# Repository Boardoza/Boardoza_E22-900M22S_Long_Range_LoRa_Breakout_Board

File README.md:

# Boardoza E22-900M22S LoRa® Breakout Board

The **Boardoza E22-900M22S Breakout Board** is a compact long-range wireless communication board based on the **Ebyte E22-900M22S** LoRa® module. Powered by the **Semtech SX1262** RF transceiver, it supports both **LoRa®** and **FSK(Frequency Shift Keying)** modulation, enabling reliable low-power wireless communication over the **850–930 MHz ISM frequency range**, including the widely used **868 MHz** and **915 MHz** bands. The onboard **32 MHz TCXO (Temperature Compensated Crystal Oscillator)** provides excellent frequency stability, making it suitable for narrowband communication and outdoor deployments.

The breakout board exposes the module's **SPI interface**, RF control signals, and status pins through standard headers, allowing easy integration with development platforms such as **STM32**, **ESP32**, **Arduino, and other 3.3V-compatible microcontrollers**. With its SMA antenna connector, industrial operating temperature range, and long communication distance, this board is ideal for **IoT gateways, smart agriculture, telemetry, environmental monitoring, industrial automation, and wireless sensor networks**.

---

## Key Features

- **Long-Range LoRa® Communication:** Based on the Semtech SX1262 transceiver for reliable long-distance wireless links.
- **868 / 915 MHz ISM Band Support:** Compatible with license-free ISM bands used worldwide.
- **High RF Output Power:** Up to **22 dBm (160 mW)** transmit power with software-adjustable output levels.
- **LoRa® and FSK Modulation Support:** Provides air data rates from 0.018 to 62.5 kbps in LoRa® mode and up to 300 kbps in FSK mode.
- **Stable RF Performance:** Integrated **32 MHz TCXO** improves frequency stability over temperature.
- **Easy MCU Integration:** Standard **4-wire SPI interface** with dedicated control and status signals.
- **SMA Antenna Connector:** Ready for external antennas with improved RF performance.
- **Ideal for IoT Applications:** Suitable for wireless sensor networks, smart agriculture, telemetry, industrial monitoring, and remote data acquisition.

---

## Technical Specifications

**Model:** E22-900M22S   
**Manufacturer:** Boardoza    
**Manufacturer IC:** Chengdu Ebyte Electronic Technology Co., Ltd.   
**RF Transceiver:** Semtech SX1262  
**Input Voltage:** 3.3V – 5.5V     
**Interface:** SPI  
**Frequency Range:** 850 – 930 MHz     
**Maximum RF Output Power:** 22 dBm (160 mW)  
**Maximum Air Data Rate (LoRa®):** 0.018 to 62.5 kbps  
**Maximum Air Data Rate (FSK):** 300 kbps  
**FIFO Buffer:** 256 Bytes  
**Oscillator:** High-Precision 32 MHz TCXO  
**Antenna Connector:** SMA Female  
**Operating Temperature:** -40°C to +85°C  
**Board Dimensions:** 40 mm × 20 mm

---

## Board Pinout

### ( J1 ) SPI Interface

| Pin Number | Pin Name | Description |
|:---:|:---:|---|
| 1 | VCC | Power Input |
| 2 | MISO | SPI Data Output |
| 3 | MOSI | SPI Data Input |
| 4 | SCK | SPI Clock |
| 5 | nCS | SPI Chip Select (Active Low) |
| 6 | GND | Ground |

### ( J2 ) Control Signals

| Pin Number | Pin Name | Description |
|:---:|:---:|---|
| 1 | NRST | Reset Input (Active Low) |
| 2 | BUSY | Module Busy Status Output |
| 3 | DIO1 | Configurable Digital I/O |

### ( J3 ) RF Switch & Control

| Pin Number | Pin Name | Description |
|:---:|:---:|---|
| 1 | RXEN | RF Receive Enable (Active High) |
| 2 | TXEN | RF Transmit Enable (Active High) |
| 3 | DIO2 | Configurable Digital I/O / RF Switch Control |

### ( J4 ) RF Connector

| Connector | Description |
|:---:|---|
| SMA Female | External 50Ω Antenna Connection |

---

## Board Dimensions

---

## Step Files

[Boardoza E22-900M22S.step](./assets/E22_900M22S%20Step.step)

---

## Datasheet

[E22-900M22S Datasheet.pdf](./assets/E22-900M22S%20Datasheet.pdf)

---

## Version History

- V1.0.0 - Initial Release

---

## Support

- If you have any questions or need support, please contact **support@boardoza.com**

---

## **License**

This repository contains both hardware and software components:

### **Hardware Design**

[![CC BY-SA 4.0][cc-by-sa-shield]][cc-by-sa]

All hardware design files are licensed under [Creative Commons Attribution-ShareAlike 4.0 International License][cc-by-sa].

[cc-by-sa]: http://creativecommons.org/licenses/by-sa/4.0/
[cc-by-sa-shield]: https://img.shields.io/badge/License-CC%20BY--SA%204.0-lightgrey.svg

### **Software/Firmware**

[![BSD-3-Clause][bsd-shield]][bsd]

All software and firmware are licensed under [BSD 3-Clause License][bsd].

[bsd]: https://opensource.org/licenses/BSD-3-Clause
[bsd-shield]: https://img.shields.io/badge/License-BSD%203--Clause-blue.svg

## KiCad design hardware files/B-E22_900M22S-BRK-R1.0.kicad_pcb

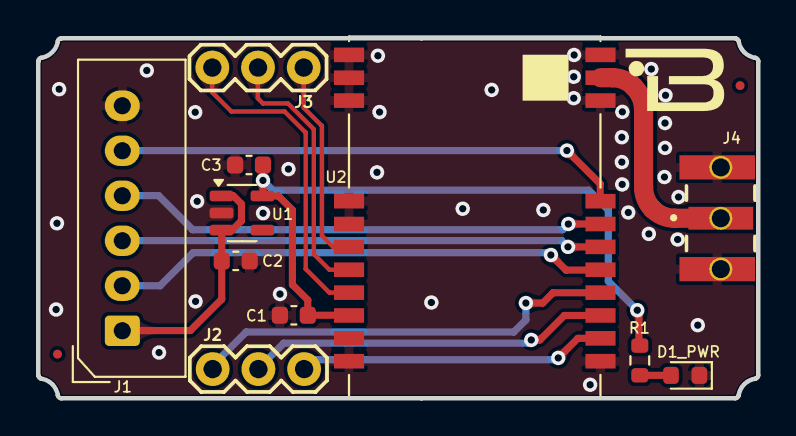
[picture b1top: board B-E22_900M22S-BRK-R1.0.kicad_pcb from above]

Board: 2 copper layers, 40.0 x 20.0 mm, 11 parts (0 on the bottom side), 15 nets.

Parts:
C1: 100nF; C_0603_1608Metric
C2, C3: 1uF; C_0603_1608Metric
D1_PWR: LED POWER; LED_0603_1608Metric
J1: 2317-06S; 2317-06S_1x06_P2.50mm_Vertical
J2, J3: CONN_03; 1X03
J4: SMA; SMA-J-P-H-ST-EM1
R1: 330R; R_0603_1608Metric
U1: TLV73333PDBVR; SOT-23-5
U2: E22-400M22S; E22-900M22S

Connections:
+3V3: C1.1, C3.1, R1.1, U1.5 (OUT), U2.P$9 (VCC)
ANT: J4.1, U2.ANT
BUSY: J2.2, U2.P$14 (BUSY)
CS: J1.5, U2.P$19 (NSS)
DIO1: J2.3, U2.P$13 (DIO1)
DIO2: J3.3, U2.P$8 (DIO2)
GND: C1.2, C2.2, C3.2, D1_PWR.1 (K), J1.6, J4.2, J4.3, U1.2 (GND), U2.P$1 (GND1), U2.P$2 (GND1), U2.P$3 (GND1), U2.P$4 (GND1), U2.P$5 (GND1), U2.P$10 (GND1), U2.P$11 (GND1), U2.P$12 (GND1), U2.P$20 (GND1), U2.P$22 (GND1)
MISO: J1.2, U2.P$16 (MISO)
MOSI: J1.3, U2.P$17 (MOSI)
NRST: J2.1, U2.P$15 (NRST)
unnamed: D1_PWR.2 (A), R1.2
RXEN: J3.1, U2.P$6 (RXEN)
SCK: J1.4, U2.P$18 (SCK)
TXEN: J3.2, U2.P$7 (TXEN)
VCC: C2.1, J1.1, U1.1 (IN), U1.3 (EN)

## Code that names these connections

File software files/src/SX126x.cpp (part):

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{
    // set pins as input or output
    if (_irq != -1) pinMode(_irq, INPUT);
    if (_txen != -1) pinMode(_txen, OUTPUT);
    if (_rxen != -1) pinMode(_rxen, OUTPUT);

    // begin spi and perform device reset
    sx126x_begin();
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 * @param reset Reset pin.
 * @param busy Busy pin.
 * @param irq IRQ pin.
 * @param txen TX enable pin.
 * @param rxen RX enable pin.
 * @return true if initialization is successful, false otherwise.
 */
bool SX126x::begin(int8_t nss, int8_t reset, int8_t busy, int8_t irq, int8_t txen, int8_t rxen)
{
    setPins(nss, reset, busy, irq, txen, rxen);
    return begin();
}

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 * @param reset Reset pin.
 * @param busy Busy pin.
 * @param irq IRQ pin.
 * @param txen TX enable pin.
 * @param rxen RX enable pin.
 */
void SX126x::setPins(int8_t nss, int8_t reset, int8_t busy, int8_t irq, int8_t txen, int8_t rxen)
{
    sx126x_setPins(nss, busy);

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}

/**
 * @brief Sets the RF IRQ pin (DIO1, DIO2, or DIO3).
 * @param dioPinSelect DIO pin selection (1, 2, or 3).
 */
void SX126x::setRfIrqPin(int8_t dioPinSelect)
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    _payloadTxRx = 0;
    sx126x_setBufferBaseAddress(_bufferIndex, _bufferIndex + 0xFF);

    // set txen pin to low and rxen pin to high
    if ((_rxen != -1) && (_txen != -1)) {
        digitalWrite(_rxen, LOW);
        digitalWrite(_txen, HIGH);
        _pinToLow = _txen;
    }
    
    sx126x_fixLoRaBw500(_bw);
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        _statusWait = SX126X_STATUS_RX_CONTINUOUS;
    }

    // set txen pin to low and rxen pin to high
    if ((_rxen != -1) && (_txen != -1)) {
        digitalWrite(_rxen, HIGH);
        digitalWrite(_txen, LOW);
        _pinToLow = _rxen;
    }

    // set device to receive mode with configured timeout, single, or continuous operation
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    if (rxPeriod > 0x00FFFFFF) rxPeriod = 0x00FFFFFF;
    if (sleepPeriod > 0x00FFFFFF) sleepPeriod = 0x00FFFFFF;

    // set txen pin to low and rxen pin to high
    if ((_rxen != -1) && (_txen != -1)) {
        digitalWrite(_rxen, HIGH);
        digitalWrite(_txen, LOW);
        _pinToLow = _rxen;
    }

    // set device to receive mode with configured receive and sleep period
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        // immediately return when interrupt signal hit
        return true;
    } else if (_statusWait == SX126X_STATUS_TX_WAIT) {
        // for transmit, calculate transmit time and set back txen pin to low
        _transmitTime = millis() - _transmitTime;
        if (_txen != -1) digitalWrite(_txen, LOW);
    } else if (_statusWait == SX126X_STATUS_RX_WAIT) {
        // for receive, get received payload length and buffer index and set back rxen pin to low
        sx126x_getRxBufferStatus(&_payloadTxRx, &_bufferIndex);
        if (_rxen != -1) digitalWrite(_rxen, LOW);
        sx126x_fixRxTimeout();
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    // calculate transmit time
    _transmitTime = millis() - _transmitTime;

    // set back txen pin to low and detach interrupt
    if (_pinToLow != -1) digitalWrite(_pinToLow, LOW);
    detachInterrupt(_irqStatic);

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 */
void SX126x::_interruptRx()
{
    // set back rxen pin to low and detach interrupt
    if (_pinToLow != -1) digitalWrite(_pinToLow, LOW);
    detachInterrupt(_irqStatic);
    sx126x_fixRxTimeout();
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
